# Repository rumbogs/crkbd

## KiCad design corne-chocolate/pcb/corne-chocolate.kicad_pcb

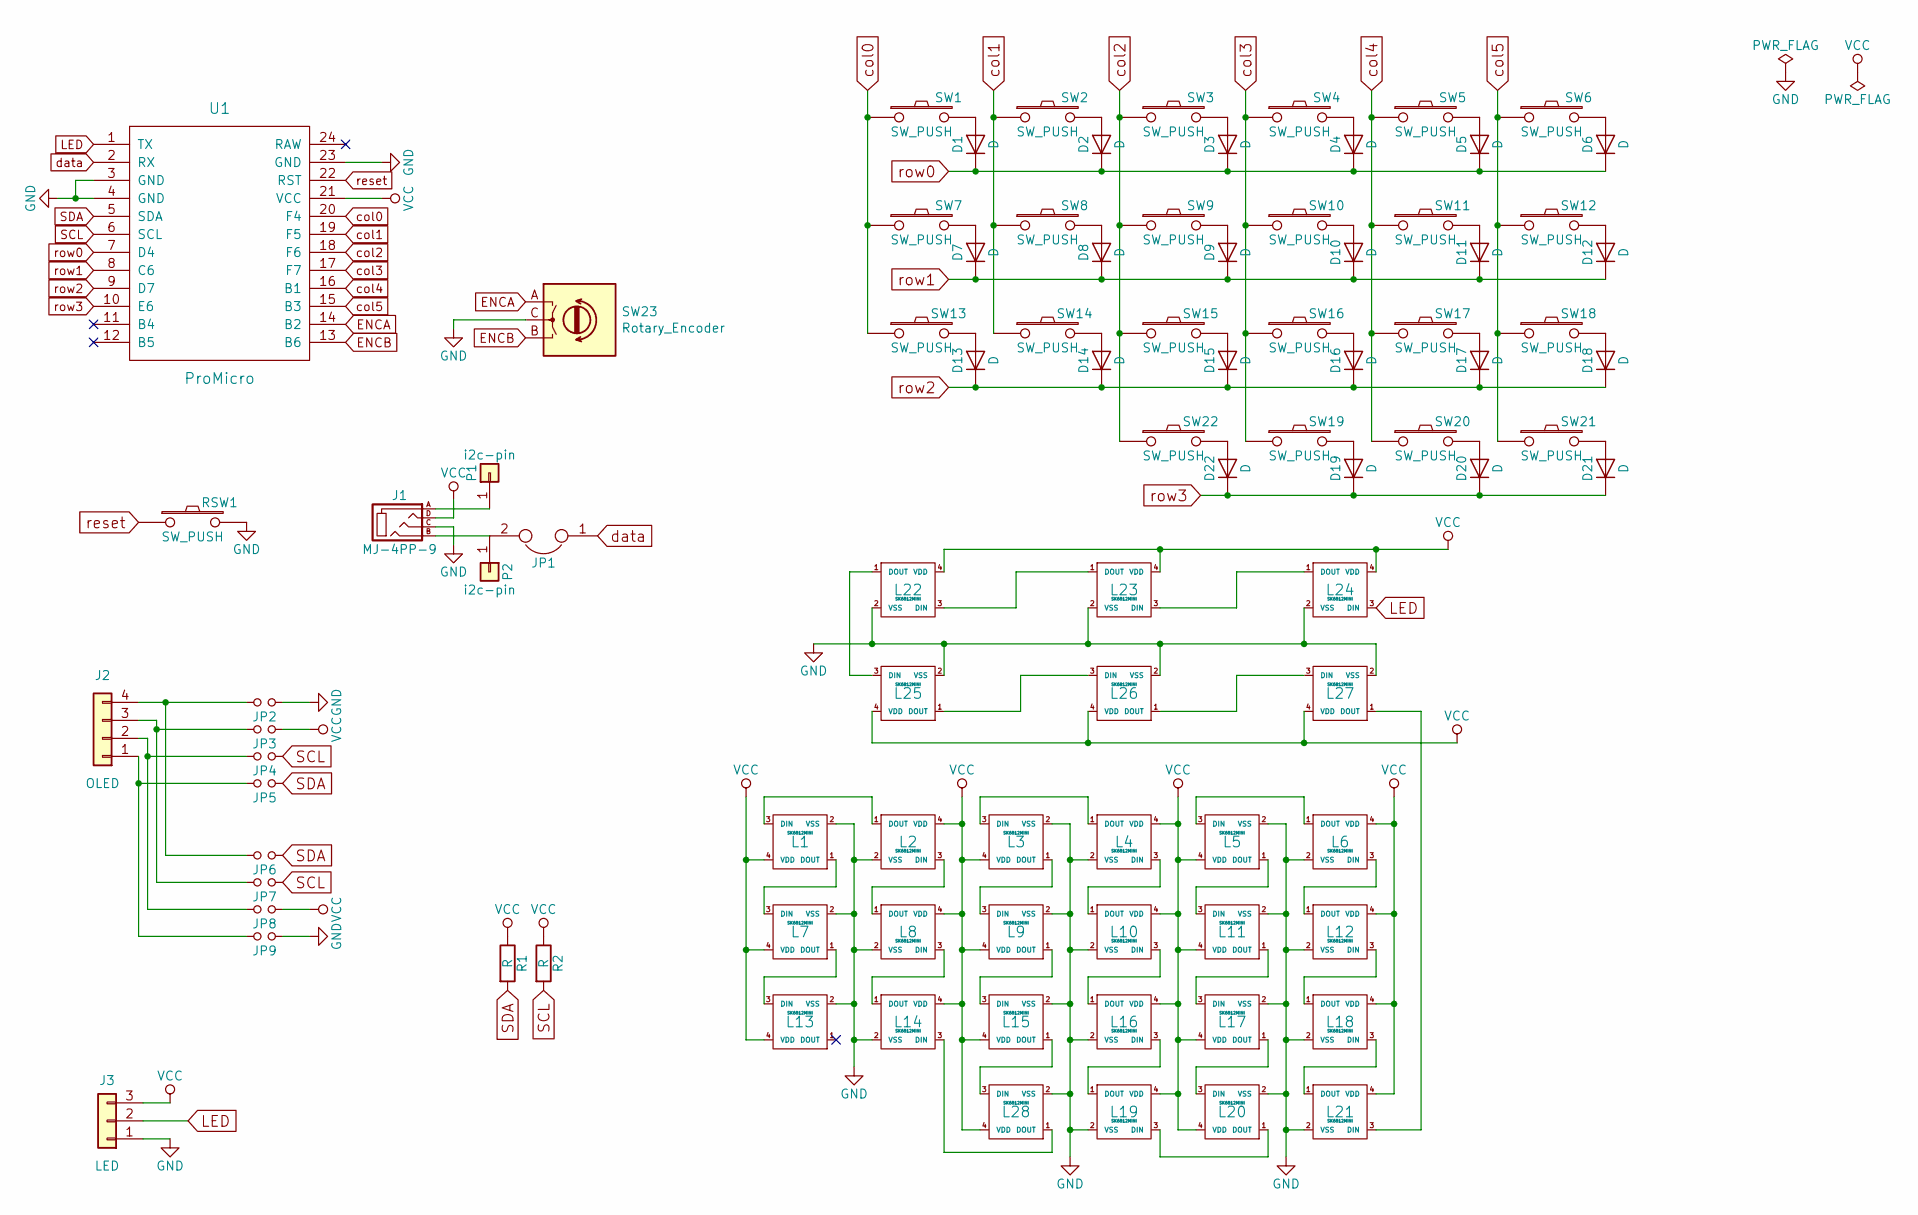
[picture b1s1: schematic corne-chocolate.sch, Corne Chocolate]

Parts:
D1, D2, D3, D4, D5, D6, D7, D8, D9, D10, D11, D12, D13, D14, D15, D16, D17, D18, D19, D20, D21, D22: D; D3_TH_SMD
J1: MJ-4PP-9
J2: OLED
J3: LED; StripLED_rev
JP1: JPC2
JP2, JP3, JP4, JP5, JP6, JP7, JP8, JP9: Jumper
L1, L2, L3, L4, L5, L6, L7, L8, L9, L10, L11, L12, L13, L14, L15, L16, L17, L18, L19, L20, L21, L28: SK6812MINI; SK6812MINI_rev
L22, L23, L24, L25, L26, L27: SK6812MINI; SK6812MINI_underglow_rev
P1, P2: i2c-pin; 1pin_conn
R1, R2: R
RSW1: SW_PUSH; ResetSW
SW1, SW2, SW3, SW4, SW5, SW6, SW7, SW8, SW9, SW10, SW11, SW12, SW13, SW14, SW15, SW16, SW17, SW18, SW19, SW20: SW_PUSH; keyswitch_cherrymx_alps_choc12_1u
SW21, SW22: SW_PUSH; keyswitch_cherrymx_alps_choc12_1.5u
SW23: Rotary_Encoder; RotaryEncoder_Alps_EC11E_Vertical_H20mm
U1: ProMicro; ProMicro_v2

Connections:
LED: J3.2, L24.3 (DIN), U1.1 (TX)
unnamed: D1.2 (A), SW1.2
unnamed: D2.2 (A), SW2.2
unnamed: D3.2 (A), SW3.2
unnamed: D4.2 (A), SW4.2
unnamed: D5.2 (A), SW5.2
unnamed: D6.2 (A), SW6.2
unnamed: D7.2 (A), SW7.2
unnamed: D8.2 (A), SW8.2
unnamed: D9.2 (A), SW9.2
unnamed: D10.2 (A), SW10.2
unnamed: D11.2 (A), SW11.2
unnamed: D12.2 (A), SW12.2
unnamed: D13.2 (A), SW13.2
unnamed: D14.2 (A), SW14.2
unnamed: D15.2 (A), SW15.2
unnamed: D16.2 (A), SW16.2
unnamed: D17.2 (A), SW17.2
unnamed: D18.2 (A), SW18.2
unnamed: D19.2 (A), SW19.2
unnamed: D20.2 (A), SW20.2
unnamed: D21.2 (A), SW21.2
unnamed: D22.2 (A), SW22.2
unnamed: J1.A, P1.1
unnamed: J1.B, JP1.2, P2.1
unnamed: J2.1, JP5.2, JP9.2
unnamed: J2.2, JP4.2, JP8.2
unnamed: J2.3, JP3.2, JP7.2
unnamed: J2.4, JP2.2, JP6.2
unnamed: L1.1 (DOUT), L7.3 (DIN)
unnamed: L1.3 (DIN), L2.1 (DOUT)
unnamed: L2.3 (DIN), L8.1 (DOUT)
unnamed: L3.1 (DOUT), L9.3 (DIN)
unnamed: L3.3 (DIN), L4.1 (DOUT)
unnamed: L5.3 (DIN), L6.1 (DOUT)
unnamed: L4.3 (DIN), L10.1 (DOUT)
unnamed: L10.3 (DIN), L16.1 (DOUT)
unnamed: L11.1 (DOUT), L17.3 (DIN)
unnamed: L5.1 (DOUT), L11.3 (DIN)
unnamed: L6.3 (DIN), L12.1 (DOUT)
unnamed: L12.3 (DIN), L18.1 (DOUT)
unnamed: L7.1 (DOUT), L13.3 (DIN)
unnamed: L8.3 (DIN), L14.1 (DOUT)
unnamed: L14.3 (DIN), L28.1 (DOUT)
unnamed: L15.1 (DOUT), L28.3 (DIN)
unnamed: L9.1 (DOUT), L15.3 (DIN)
unnamed: L16.3 (DIN), L19.1 (DOUT)
unnamed: L17.1 (DOUT), L20.3 (DIN)
unnamed: L18.3 (DIN), L21.1 (DOUT)
unnamed: L19.3 (DIN), L20.1 (DOUT)
unnamed: L21.3 (DIN), L27.1 (DOUT)
unnamed: L22.1 (DOUT), L25.3 (DIN)
unnamed: L22.3 (DIN), L23.1 (DOUT)
unnamed: L23.3 (DIN), L24.1 (DOUT)
unnamed: L25.1 (DOUT), L26.3 (DIN)
unnamed: L26.1 (DOUT), L27.3 (DIN)
SCL: JP4.1, JP7.1, R2.2, U1.6 (SCL)
SDA: JP5.1, JP6.1, R1.2, U1.5 (SDA)
VCC: J1.D, J3.3, JP3.1, JP8.1, L1.4 (VDD), L2.4 (VDD), L3.4 (VDD), L4.4 (VDD), L5.4 (VDD), L6.4 (VDD), L7.4 (VDD), L8.4 (VDD), L9.4 (VDD), L10.4 (VDD), L11.4 (VDD), L12.4 (VDD), L13.4 (VDD), L14.4 (VDD), L15.4 (VDD), L16.4 (VDD), L17.4 (VDD), L18.4 (VDD), L19.4 (VDD), L20.4 (VDD), L21.4 (VDD), L22.4 (VDD), L23.4 (VDD), L24.4 (VDD), L25.4 (VDD), L26.4 (VDD), L27.4 (VDD), L28.4 (VDD), R1.1, R2.1, U1.21 (VCC)
col0: SW1.1, SW7.1, SW13.1, U1.20 (F4)
col1: SW2.1, SW8.1, SW14.1, U1.19 (F5)
col2: SW3.1, SW9.1, SW15.1, SW22.1, U1.18 (F6)
col3: SW4.1, SW10.1, SW16.1, SW19.1, U1.17 (F7)
col4: SW5.1, SW11.1, SW17.1, SW20.1, U1.16 (B1)
col5: SW6.1, SW12.1, SW18.1, SW21.1, U1.15 (B3)
data: JP1.1, U1.2 (RX)
reset: RSW1.1, U1.22 (RST)
row0: D1.1 (K), D2.1 (K), D3.1 (K), D4.1 (K), D5.1 (K), D6.1 (K), U1.7 (D4)
row1: D7.1 (K), D8.1 (K), D9.1 (K), D10.1 (K), D11.1 (K), D12.1 (K), U1.8 (C6)
row2: D13.1 (K), D14.1 (K), D15.1 (K), D16.1 (K), D17.1 (K), D18.1 (K), U1.9 (D7)
row3: D19.1 (K), D20.1 (K), D21.1 (K), D22.1 (K), U1.10 (E6)

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
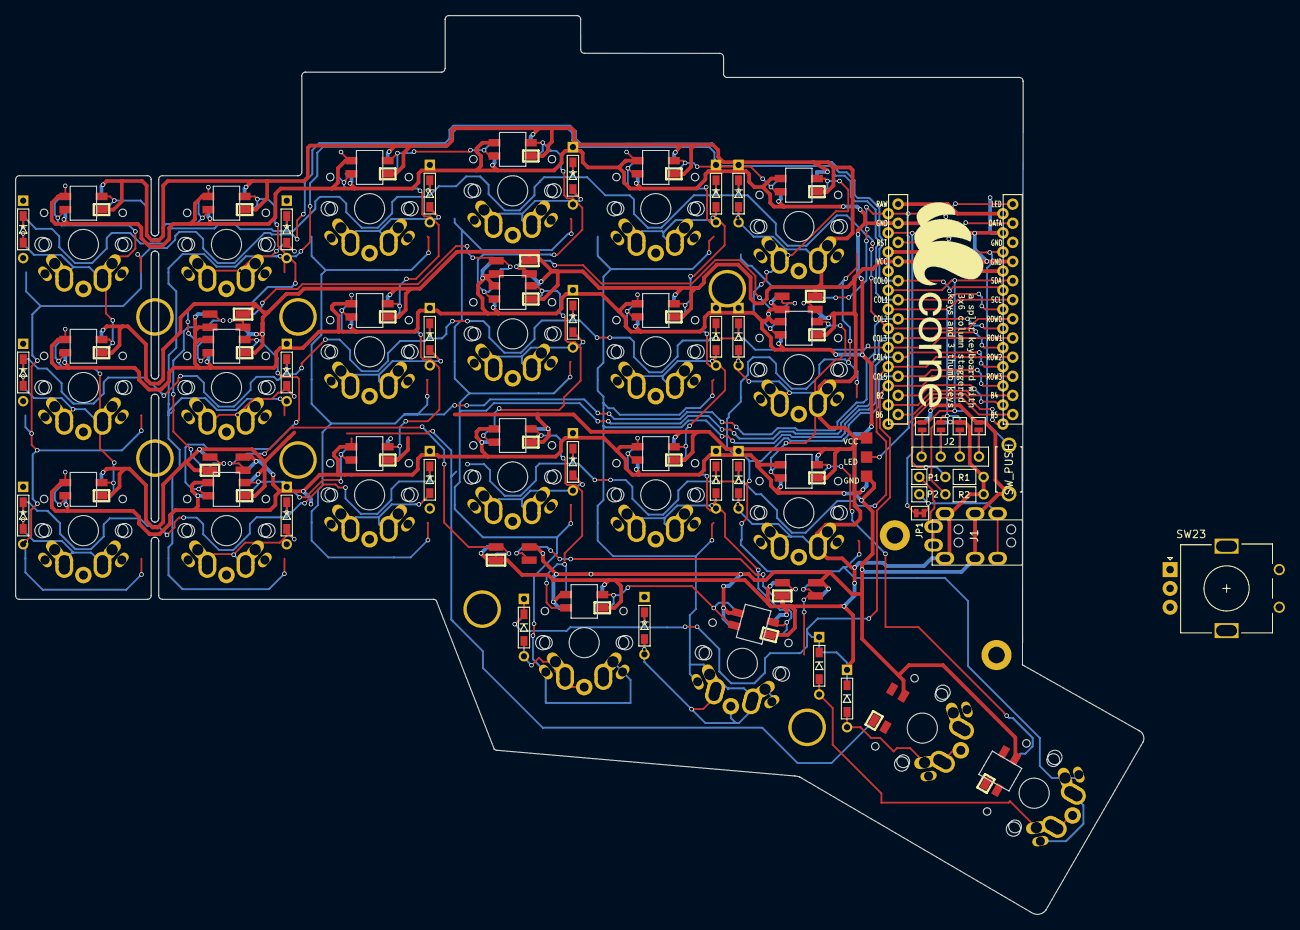
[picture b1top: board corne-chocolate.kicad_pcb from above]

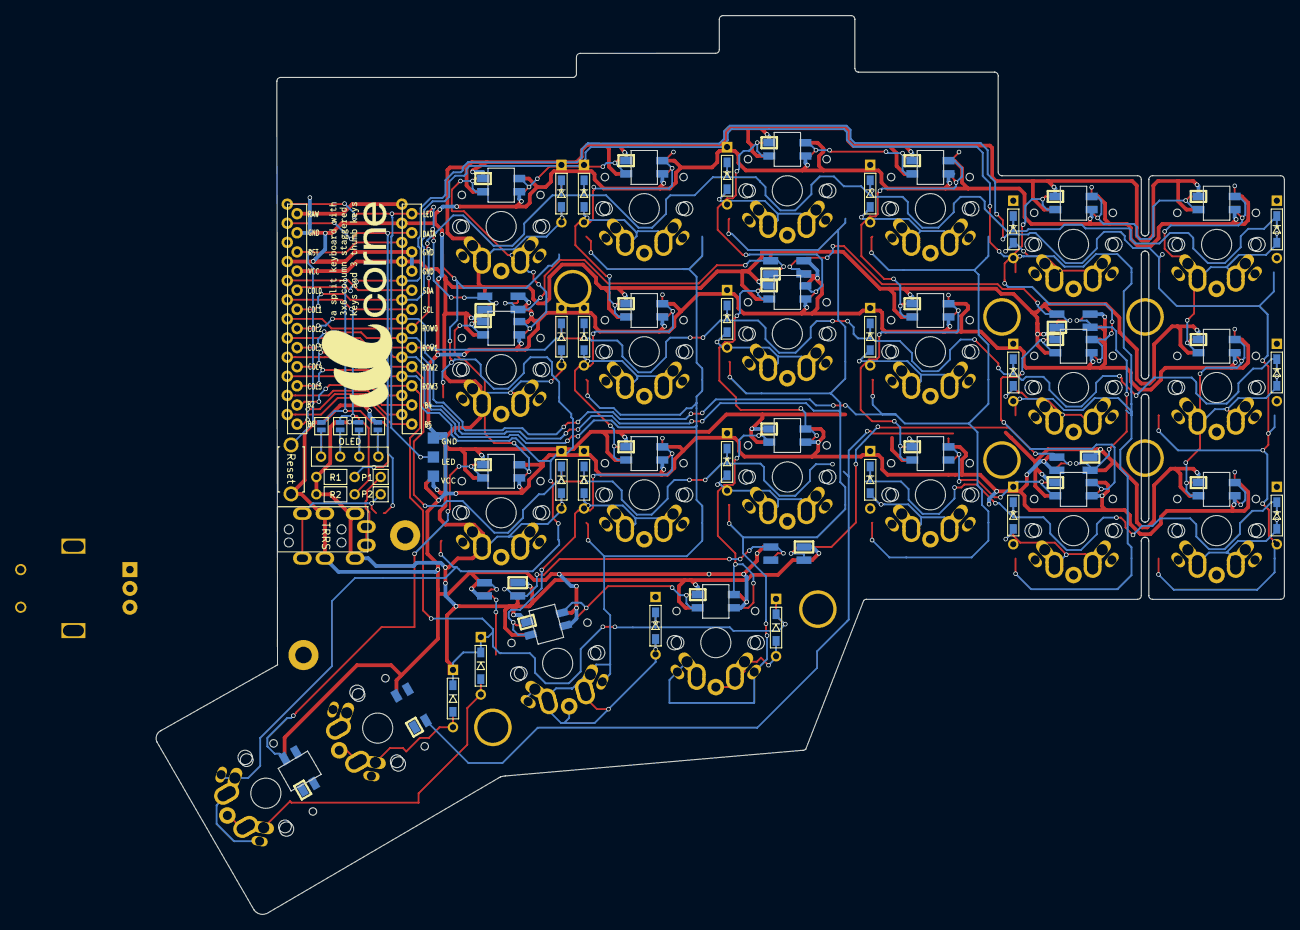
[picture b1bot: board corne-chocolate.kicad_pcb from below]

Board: 2 copper layers, 149.8 x 119.3 mm, 91 parts (4 on the bottom side), 72 nets.

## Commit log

2020-11-24 Before wiring
2020-11-25 Finished left hand pcb
2021-06-23 add new stuff
